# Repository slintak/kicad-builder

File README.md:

# kicad-builder Docker Image

A ready-to-use Docker image for building, documenting, and rendering static
websites and manufacturing files for KiCAD hardware projects. This container
is designed for both CI/CD environments (such as GitHub Actions) and manual
use by hardware developers who want reproducible, automated documentation
and manufacturing outputs.

## Features

- Ubuntu 26.04 LTS base
- KiCad 10.0.8 (from the official KiCad PPA)
- `kicad-fab`: one command makes all fabrication and release files of a KiCad
  project for JLCPCB (see [Fabrication pipeline](#fabrication-pipeline-kicad-fab))
- KiKit for Gerber, panel and PCB fabrication outputs
- PcbDraw for high-quality PCB renders
- LaTeX tools for PDF docs
- Tools for:
    - Board image rendering
    - BOM generation (including JLCPCB CSV support)
    - Markdown to HTML site generation (with Jinja2, markdown-cli)
    - Static web build (rsync, xsltproc, etc.)
- Designed for GitHub Actions, but also convenient for manual use

## Usage: In GitHub Actions

Add this to your `.github/workflows/ci.yml` file:

```yaml
name: CI
on:
  push:
    branches: [ main ]
jobs:
  build-web:
    runs-on: ubuntu-latest
    container:
      image: ghcr.io/slintak/kicad-builder:latest
    steps:
      - name: Checkout repository
        uses: actions/checkout@v4
      - name: Build your site or artifacts
        run: make web  # or whatever your build command is
```

For the fabrication files, use the reusable workflows (see [CI for board repositories](#ci-for-board-repositories)).

## Usage: Manually

Build the image (optional, only if customizing):

```
make build
```

Run an interactive shell in the container:

```
make run
```

This opens a shell in /workspace (the default working directory).

(Recommended) Mount your project directory:

```
docker run --rm -it -v $PWD:/workspace ghcr.io/slintak/kicad-builder:latest /bin/bash
```

With no command, the image runs `kicad-fab build /workspace`:

```
docker run --rm -u "$(id -u):$(id -g)" -v "$PWD":/workspace ghcr.io/slintak/kicad-builder:latest
```

## Fabrication pipeline (kicad-fab)

`kicad-fab` takes a KiCad project directory and makes the checks and the files to
order and to release the board. The same command runs on your computer and in
GitHub Actions. A project needs only its KiCad files, an optional `panel.json`
(KiKit preset) and an optional `kicad-fab.toml`.

```
kicad-fab build [DIR]       # all checks and all outputs, then the release ZIP (DIR: default .)
kicad-fab check [DIR]       # ERC, DRC, schematic parity, BOM field checks, panel checks
kicad-fab schematic|bom|pos|gerbers|panel|step|render|zip [DIR]
kicad-fab versions          # tool versions as JSON
```

Options: `--out DIR` (default `DIR/build`), `--wip`, `--release-version TEXT`
(default: `git describe`), and for `build`: `--skip schematic,panel,panel-render,step,render,zip`
(`render` is the board renders, `panel-render` the panel PNG, `zip` the release ZIP;
leave the release ZIP out when a CI artifact already holds the files).

ERC and DRC items that are excluded in KiCad (right click > Exclude, stored in the project or board) are not checked.
The exit code is not 0 if a check finds an error. `build` makes all outputs also
when a check fails, then it puts `DO-NOT-ORDER.txt` into the fab directories and ZIP
files and gives exit code 1.

Work in progress: `--wip`, `wip = true` in `kicad-fab.toml`, or a text in the KiCad
text variable `WIP_MARK` (used by the M17 board library). Then layout DRC errors are
warnings, and every fab directory and ZIP file gets `DO-NOT-ORDER.txt`. ERC and
schematic parity stay strict.

### Outputs

```
build/
  manifest.json                    versions (image, KiCad, KiKit), git describe, date, files, check results
  reports/erc.json drc.json panel-check.json
  <board>_schematic.pdf
  bom/<board>_bom_jlcpcb.csv       Comment,Designator,Footprint,LCSC Part #   (one board)
  bom/<board>_bom_mouser.csv       Mouser Part Number,Manufacturer Part Number,Quantity,Customer Part Number,Description,Manufacturer
  bom/<board>_bom_alternates.csv   References,Quantity,Primary MPN,Alt Manufacturer,Alt MPN,Alt Mouser Part Number,Alt LCSC
  bom/<board>_bom_other.csv        parts with no LCSC and no Mouser number
  fab/<board>_gerbers.zip          Gerbers and drill files of one board
  fab/<board>_pos_jlcpcb.csv       Designator,Mid X,Mid Y,Layer,Rotation (Top/Bottom, mm)
  panel/<board>_panel.kicad_pcb    KiKit panel (only with panel.json)
  panel/<board>_panel_gerbers.zip
  panel/<board>_panel_bom_jlcpcb.csv
  panel/<board>_panel_pos_jlcpcb.csv
  panel/<board>_panel.png
  <board>.step.xz
  render/<board>-top.png -bottom.png -preview.png
  <board>-<version>.zip            all files above, for the release
```

The Mouser quantity is the quantity on one board x `boards` + spares. "Customer
Part Number" has the references. The Mouser BOM tool accepts 99 lines; kicad-fab
gives a warning above this.

DNP parts and parts with "exclude from BOM", "exclude from board" or "exclude from
position files" are not in the assembly files (JLCPCB BOM and CPL). Parts in
`assembly.exclude` are not in the assembly files, but they stay in the Mouser order.

### Configuration: kicad-fab.toml

All keys are optional. These are the defaults:

```toml
fab_house = "jlcpcb"
boards = 10                      # quantity for the Mouser order file
spares = { "0402" = 10, "0603" = 5, default = 0 }   # extra parts per line, by footprint name
wip = false
strict = false                   # true: KiCad ERC and DRC warnings are errors too
version = ""                     # release version; empty: git describe
# project = "name"               # only if the directory has more than one .kicad_pro

[fields]                         # first field with a value wins
lcsc = ["LCSC", "LCSC Part #", "JLCPCB Part #"]
mouser = ["Mouser", "Mouser Part Number"]
mpn = ["MPN", "Manufacturer Part Number"]
manufacturer = ["Manufacturer"]
description = ["Description"]
source = ["Source"]
alt_prefix = "Alt "              # Alt LCSC, Alt Mouser, Alt MPN, Alt Manufacturer
correction = "JLCPCB_CORRECTION" # rotation and offset correction, KiKit format "x;y;rotation"

[assembly]
exclude = []                     # references the assembler must not place, for example ["J1", "J2"]
sides = "auto"                   # auto, both, top, bottom, or none (bare PCB: no assembly files)

[panel]
file = "panel.json"              # KiKit preset; no file: no panel
vcut_layer = "User.Comments"     # layer of the V-cuts in KiCad (Cmts.User)
designators = "unique"           # "unique": C1_1..C1_n in the panel CPL and BOM; "repeat": C1 n times
ignore = []                      # panel check rules that only give a warning, for example ["copper_edge"]

[render]
args = ["--quality", "high", "--background", "transparent", "-w", "1440", "-h", "1080"]
```

Alt fields have one value per alternate, separated by commas. Use `-` for no value,
for example `Alt LCSC = "C100006, -"`.

### JLCPCB rules

kicad-fab follows these JLCPCB rules (from the JLCPCB KiCad guide, the Gerber
preparation page, the ordering guide and the V-cut and panel standards, 2026-11):

Gerbers and drill files:

* Protel file extensions as KiCad writes them (`gtl`, `g1`, `g2`, ..., `gbl`, `gts`,
  `gbs`, `gto`, `gbo`, `gtp`, `gbp`), one outline file (`gm1`, Edge.Cuts), no other
  mechanical or user layer files, netlist attributes, format 4.6, mm.
* Excellon drill files, mm, decimal format, PTH and NPTH in separate files.
* Gerbers, drill files and positions use one origin: the lower left corner of the board (or panel) outline. All coordinates are positive.

V-cuts:

* JLCPCB reads V-cuts only from the outline layer. A V-cut line in a separate
  `CmtUser` Gerber is ignored, and the panel arrives without V-cuts.
* In KiCad the V-cuts stay on their own layer (`vcut_layer`), so that the DRC of the
  panel passes. For the panel Gerbers, kicad-fab moves the V-cut lines and their
  "V-CUT" labels into the outline Gerber. It does not plot the V-cut layer.
* The panel check: lines are straight, horizontal or vertical, and cross the whole
  panel (no jump V-cut), max. 25 per axis, parallel lines >= 2 mm apart, copper
  >= 0.4 mm from the centre line (warning below 1.0 mm), board thickness >= 0.6 mm.

Panel for SMT assembly ("Panel by Customer"):

* Panel 70 x 70 mm to 250 x 250 mm, rails >= 5 mm.
* 3 or 4 fiducials on each assembled side: 1 mm copper, 2 mm mask opening, centre
  >= 3.85 mm from the panel edge.
* NPTH tooling holes: 3 holes of 1.152 mm (KiKit `:jlcTooling`) or 2 mm (warning otherwise).
* Mouse bites: holes 0.5 to 0.8 mm, 0.2 to 0.3 mm between the holes; routed gap >= 2 mm.
* Copper >= 0.2 mm from a routed edge.

`kicad-fab check` writes the results to `reports/panel-check.json` and fails on the
hard rules. The warnings do not fail.

Assembly files and panel designators:

* KiKit makes the panel with `renameref = "{orig}"`. kicad-fab sets this and gives
  a warning if `panel.json` has another value. Thus the silkscreen of every board
  copy shows the original references (C1, not C1_0).
* JLCPCB accepts each designator only once. With `designators = "unique"`, the panel
  CPL and panel BOM rename the parts only in the CSV files: C1 on copy n is `C1_n`
  (copies in rows from the top left). The PCB is not changed.
* The BOM comes from the schematic of the single board. The panel positions come
  from the panel PCB. kicad-fab finds the copies from the footprint positions, not
  from the references.
* Positions use the KiKit logic: relative to the aux origin, Y up, bottom side
  rotation mirrored, `JLCPCB_CORRECTION` applied.

### CI for board repositories

The repository has two reusable workflows.

`board.yml` makes all files and uploads `build/` as an artifact:

```yaml
# .github/workflows/fab.yml in a board repository
name: Fabrication files
on:
  push:
  pull_request:
jobs:
  fab:
    uses: slintak/kicad-builder/.github/workflows/board.yml@main
    with:
      image: ghcr.io/slintak/kicad-builder:10.0.8   # optional
      directory: .                                  # optional, directory of the .kicad_pro
```

`release-board.yml` runs on a tag on the default branch. It makes all files and a
GitHub release with the renders in the release text, the commits since the previous
tag, and the release ZIP (Gerbers of the board and the panel, BOMs, CPLs, STEP,
renders, schematic PDF, manifest):

```yaml
# .github/workflows/release.yml in a board repository
name: Release
on:
  push:
    tags: ["v*"]
jobs:
  release:
    uses: slintak/kicad-builder/.github/workflows/release-board.yml@main
    permissions:
      contents: write
```

A release of a board with `DO-NOT-ORDER.txt` (work in progress or check errors) is
marked as a pre-release.

### Tests

The tests use a small demo board in `tests/projects/demo` (4 layers, 2 x 2 panel
with V-cuts). The script `tools/make_demo_board.py` makes it (`make demo`). The
tests run in the image:

```
make build TAGS=dev
make test TAG=dev
```

## Versions

The `latest` tag and the `10.0.8` tag contain these versions:

| Tool | Version |
| --- | --- |
| Ubuntu | 26.04 LTS |
| KiCad | 10.0.8 (PPA `kicad/kicad-10.0-releases`) |
| Python | 3.14 (Ubuntu package) |
| kicad-fab | 1.0.5 (this repository) |
| KiKit | 1.8.1 and later fixes from master, commit `2aa564ff6019560e18553b2c7d16c875fa417d63` |
| PcbDraw | fork `slintak/PcbDraw`, commit `3dd07c63179172746e9f28facd8800814c2185a1` |
| mistune | 2.0.5 |
| jinja2-cli | 1.0.1 |
| Markdown | 3.10.3 |
| PyYAML | 6.0.3 |
| pytest | 9.0.2 |
| Pillow | from Ubuntu (python3-pil) |

The KiKit commit has fixes for KiCad 10 that are not in a KiKit release yet:

* A workaround for the KiCad SWIG iterator change.
* KiKit keeps KiCad 10 variants in generated panels.
* Tab fillets on curved and finely segmented board outlines, and faster panels.

Image tags: `latest` (from the main branch), `<KiCad version>` (for example `10.0.8`)
and `<KiCad version>-<kicad-fab version>` (for example `10.0.8-1.0.5`, from the tag
`v1.0.5`). Use a version tag in CI if you want the same tools in every build.
Each week, a CI job tries the newest KiCad 10 package and KiKit release and opens
an issue if the tests fail.

## Python packages

Ubuntu 24.04 and newer mark the system Python as "externally managed" (PEP 668).
The image installs KiKit and PcbDraw into the system Python. They need the `pcbnew`
module from the KiCad package. The image sets `PIP_BREAK_SYSTEM_PACKAGES=1`.
Thus `pip install` works in your CI job without extra flags.

## Included tools

* KiCad 10.0.8, with the symbol, footprint and 3D model libraries
* kicad-fab
* KiKit
* PcbDraw
* Python 3, pip, pytest, Markdown and jinja2-cli
* LaTeX (pdflatex, latexmk, pdfjam) and pandoc
* xsltproc, rsync, cmark, librsvg2-bin, xz-utils and more

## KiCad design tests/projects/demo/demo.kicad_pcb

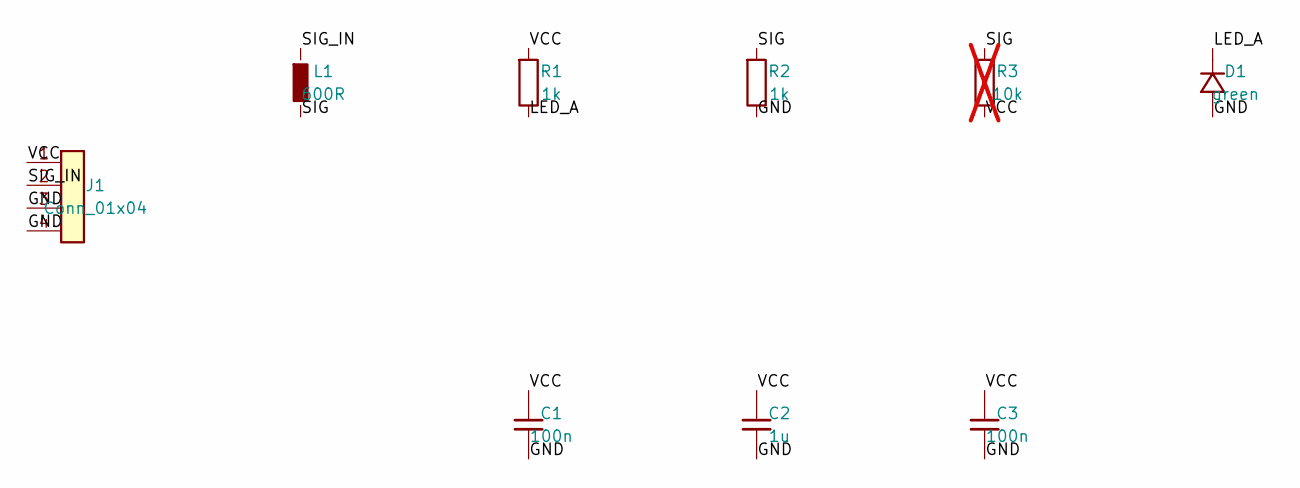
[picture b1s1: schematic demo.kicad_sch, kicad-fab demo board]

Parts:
C1, C3: 100n; C_0402; MPN DEMO-C100N-0402; LCSC C100002
C2: 1u; C_0402; MPN DEMO-C1U-0402; LCSC C100005
D1: green; LED_0603; MPN DEMO-LED-G-0603; LCSC C100004
J1: Conn_01x04; PinHeader_1x04_P2.54mm; MPN DEMO-HDR-1X04; Mouser 000-DEMO-HDR4
L1: 600R; L_0603
R1, R2: 1k; R_0402; MPN DEMO-R1K-0402; LCSC C100001
R3: 10k; R_0402; MPN DEMO-R10K-0402; LCSC C100003; not fitted

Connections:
/GND: C1.2, C2.2, C3.2, D1.1, J1.3, J1.4, R2.2
/LED_A: D1.2, R1.2
/SIG: L1.2, R2.1, R3.1
/SIG_IN: J1.2, L1.1
/VCC: C1.1, C2.1, C3.1, J1.1, R1.1, R3.2

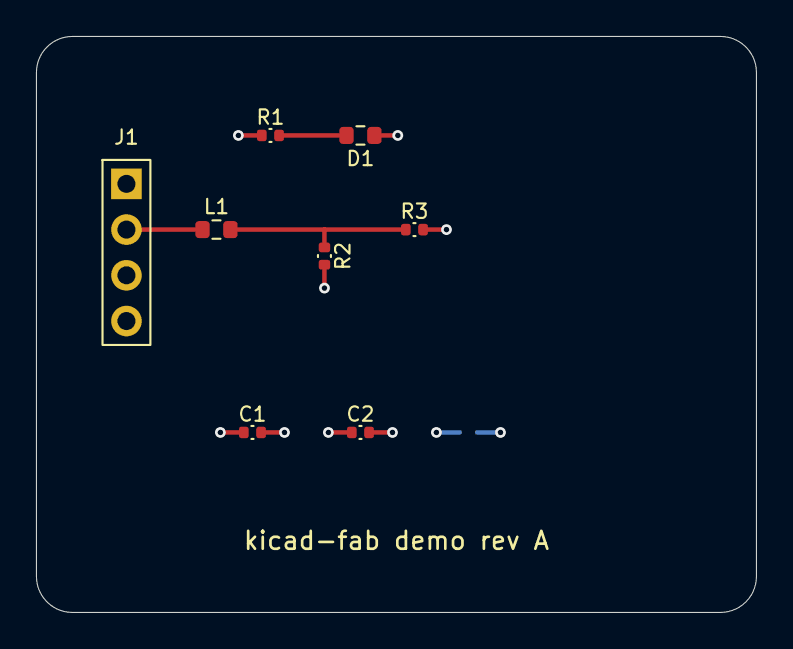
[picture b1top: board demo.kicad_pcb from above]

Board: 4 copper layers, 40.0 x 32.0 mm, 9 parts (1 on the bottom side), 5 nets.

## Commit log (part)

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2025-07-30 Added Dockerfile, Makefile and documentation
2025-08-26 Added `pandoc` for rendering Markdown docs
2026-01-29 Add `texlive-extra-utils` for `pdfjam` tool
2026-01-29 Slim image by skipping recommends and pip cache
    Use --no-install-recommends for apt installs, add gnupg for PPA keys, and disable pip cache. This drops the image from ~7.74GB to ~1.82GB in our build.
2026-01-29 Install KiCad libraries explicitly
    Add kicad-footprints, kicad-packages3d, and kicad-symbols to restore SMD 3D models when using --no-install-recommends.
    Back at 7.1 GB.
